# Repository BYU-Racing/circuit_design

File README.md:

# circuit_design
All of the low voltage circuit schematics and PCB designs

Deprecated designs are in the 2024 folder, all new stuff is in 2025

cheeseburger

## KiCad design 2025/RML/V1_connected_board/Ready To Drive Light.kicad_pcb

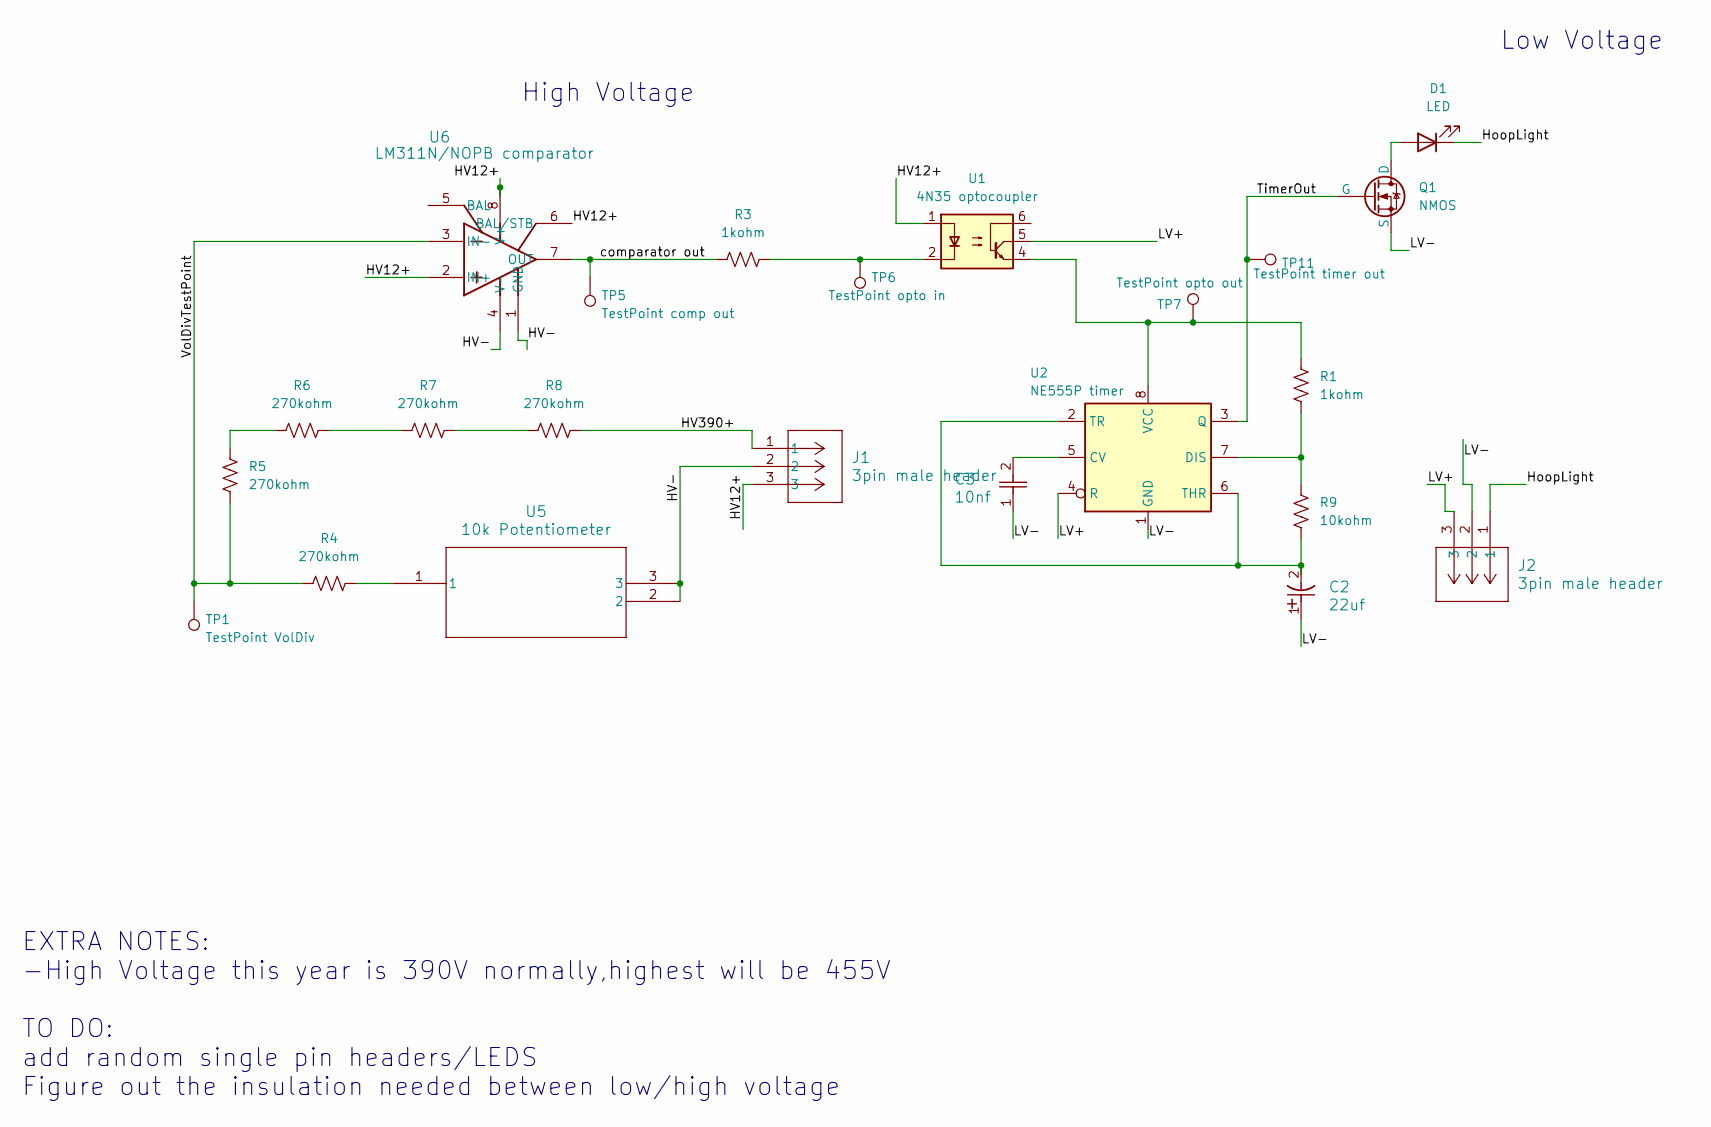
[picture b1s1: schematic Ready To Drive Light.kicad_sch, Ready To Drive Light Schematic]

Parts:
C2: 22uf; PCAP_16x20-THRU-ELECT_NCA
C3: 10nf; CAP_B32021_TDK
D1: LED; LED_D5.0mm_FlatTop
J1, J2: 3pin male header; CONN_G800W305xxxEU_AMP
Q1: NMOS; TO220AB_VIS
R1, R3: 1kohm; R_Axial_DIN0207_L6.3mm_D2.5mm_P7.62mm_Horizontal
R4, R5, R6, R7, R8: 270kohm; R_Axial_DIN0207_L6.3mm_D2.5mm_P7.62mm_Horizontal
R9: 10kohm; R_Axial_DIN0207_L6.3mm_D2.5mm_P7.62mm_Horizontal
TP1: TestPoint VolDiv; TestPoint_Loop_D2.60mm_Drill1.4mm_Beaded; PARTREV A
TP5: TestPoint comp out; TestPoint_Loop_D2.60mm_Drill1.4mm_Beaded
TP6: TestPoint opto in; TestPoint_Loop_D2.60mm_Drill1.4mm_Beaded
TP7: TestPoint opto out; TestPoint_Loop_D2.60mm_Drill1.4mm_Beaded
TP11: TestPoint timer out; TestPoint_Loop_D2.60mm_Drill1.4mm_Beaded
U1: 4N35 optocoupler; DIP-6_W7.62mm
U2: NE555P timer; DIP-8_W7.62mm
U5: 10k Potentiometer; 3296W-1-103_BRN
U6: LM311N/NOPB comparator; N08E

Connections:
/HV12+: J1.3, U1.1, U6.2 (IN+), U6.6 (BAL/STB), U6.8 (V+)
/HV390+: J1.1, R8.2
/HV-: J1.2, U5.2, U5.3, U6.1 (GND), U6.4 (V-)
/HoopLight: D1.1 (K), J2.1
/LV+: J2.3, U1.5, U2.4 (R)
/LV-: C2.1, C3.1, J2.2, Q1.3 (S), U2.1 (GND)
/TimerOut: Q1.2 (G), TP11.1, U2.3 (Q)
/VolDivTestPoint: R4.1, R5.1, TP1.1, U6.3 (IN-)
/comparator out: R3.1, TP5.1, U6.7 (OUT)
unnamed: D1.2 (A), Q1.1 (D)
unnamed: R3.2, TP6.1, U1.2
unnamed: R4.2, U5.1
unnamed: R5.2, R6.1
unnamed: R6.2, R7.1
unnamed: R7.2, R8.1
unnamed: C3.2, U2.5 (CV)
unnamed: R1.1, R9.2, U2.7 (DIS)
unnamed: C2.2, R9.1, U2.2 (TR), U2.6 (THR)
unnamed: R1.2, TP7.1, U1.4, U2.8 (VCC)

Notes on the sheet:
Low Voltage
EXTRA NOTES: -High Voltage this year is 390V normally,highest will be 455V TO DO: add random single pin headers/LEDS Figure out the insulation needed between low/high voltage
High Voltage

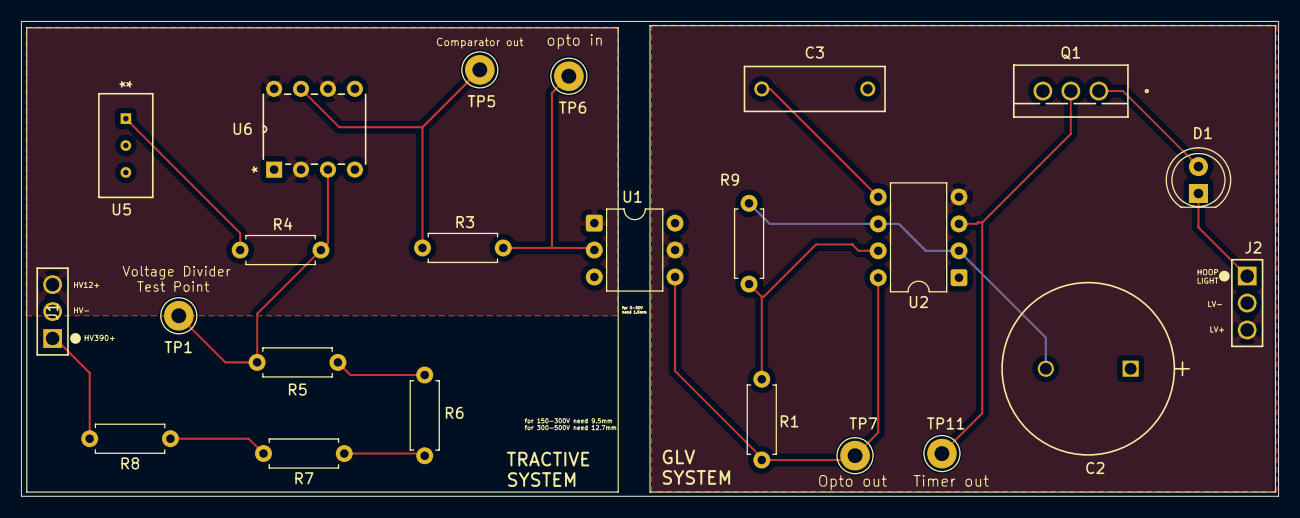
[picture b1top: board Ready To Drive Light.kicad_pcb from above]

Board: 2 copper layers, 118.6 x 44.8 mm, 23 parts (0 on the bottom side), 19 nets.

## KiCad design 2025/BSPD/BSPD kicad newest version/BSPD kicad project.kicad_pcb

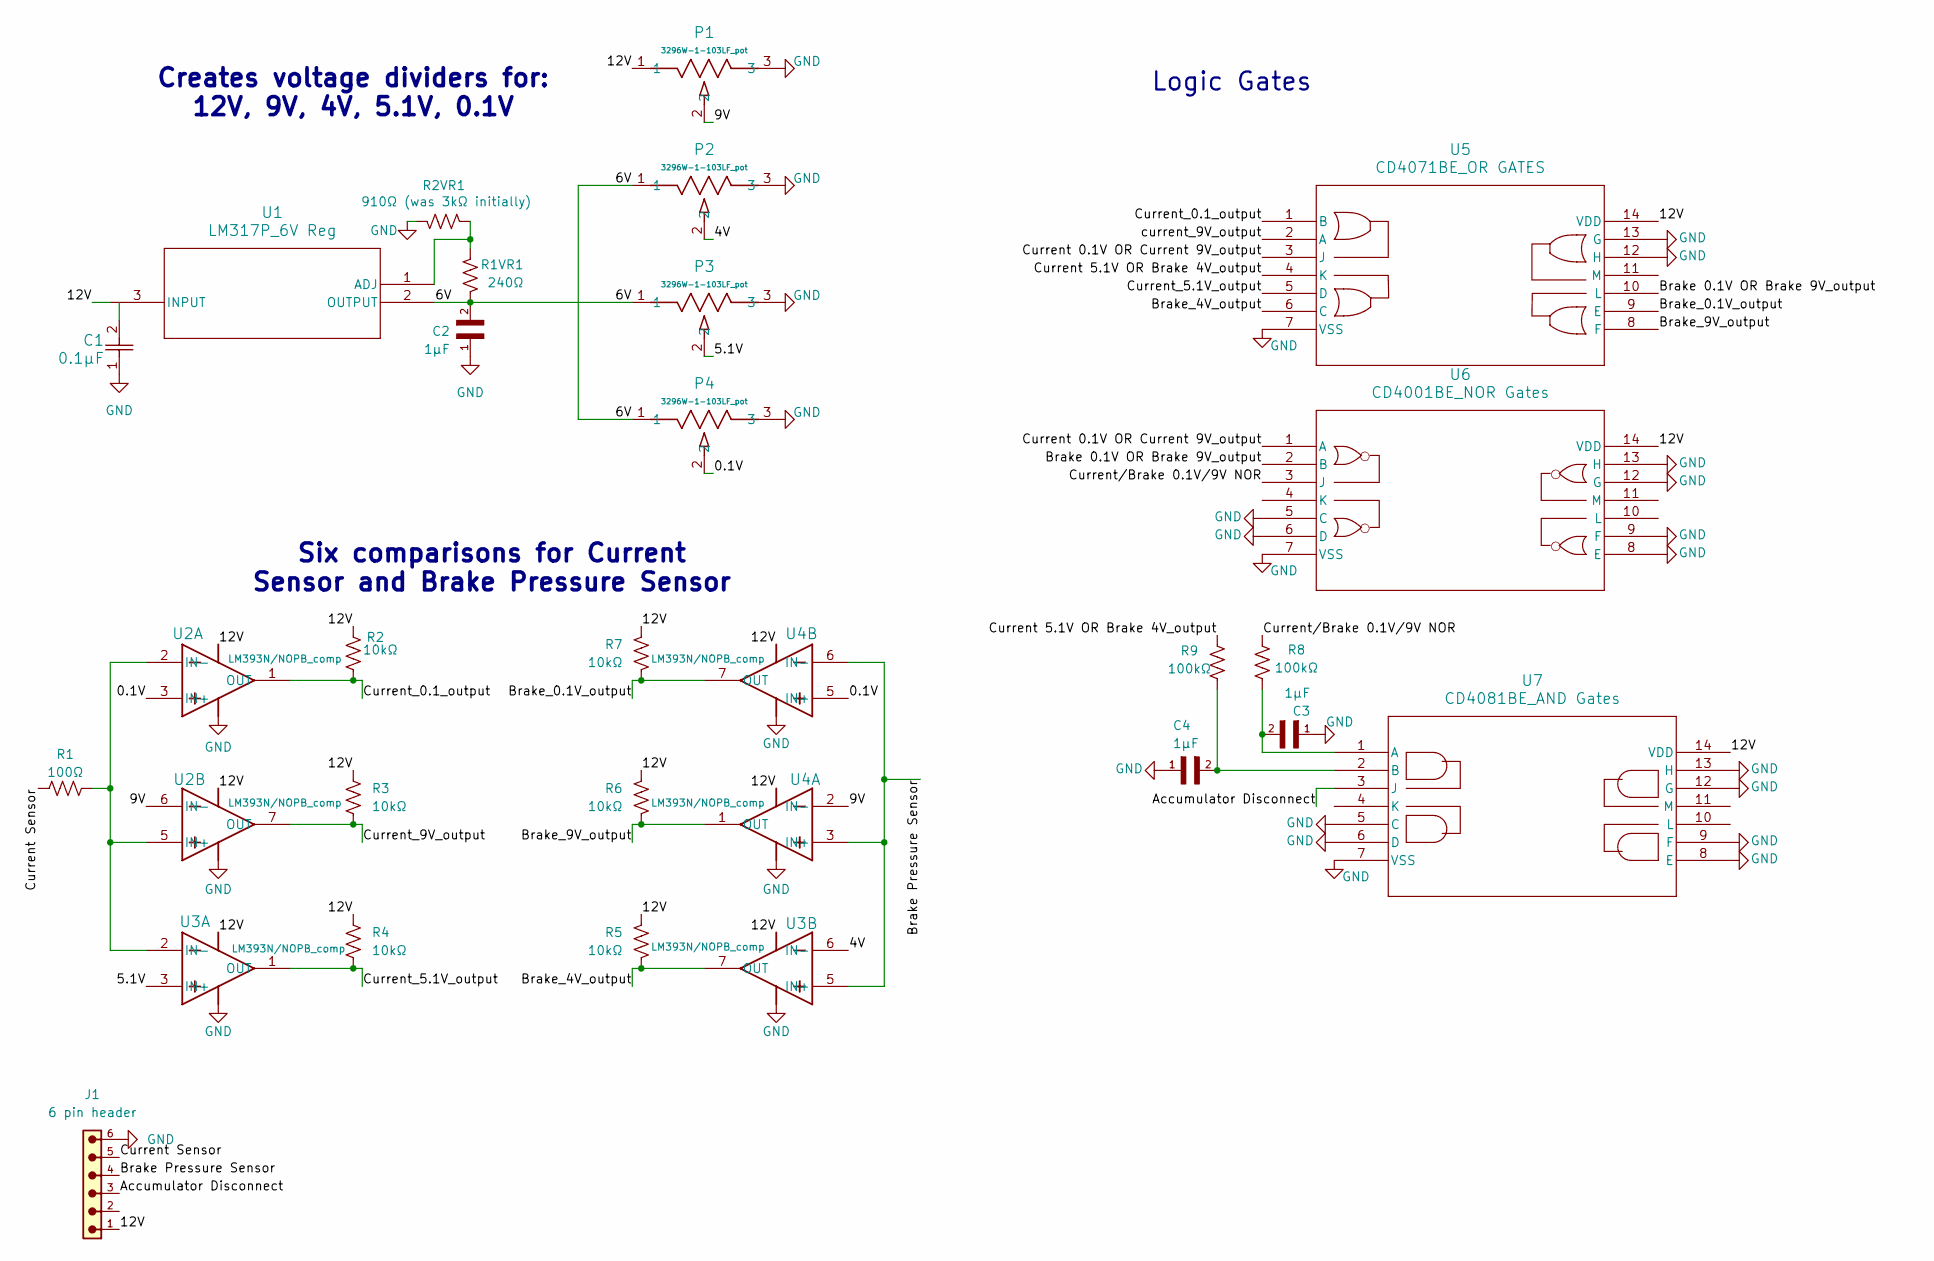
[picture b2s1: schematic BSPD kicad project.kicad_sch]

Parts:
C1: 0.1µF; K104K10X7RF5UH5_VIS
C2, C3, C4: 1µF; CAP_RCER72A105K2DBH03A; PARTREV Mar. 2018
J1: 6 pin header; PinHeader_1x06_P1.00mm_Vertical
P1, P2, P3, P4: 3296W-1-103LF_pot; POT_3296W
R1: 100Ω; R_Axial_DIN0204_L3.6mm_D1.6mm_P5.08mm_Horizontal
R1VR1: 240Ω; R_Axial_DIN0204_L3.6mm_D1.6mm_P5.08mm_Horizontal
R2, R3, R4, R5, R6, R7: 10kΩ; R_Axial_DIN0204_L3.6mm_D1.6mm_P5.08mm_Horizontal
R2VR1: 910Ω (was 3kΩ initially); R_Axial_DIN0204_L3.6mm_D1.6mm_P5.08mm_Horizontal
R8, R9: 100kΩ; R_Axial_DIN0204_L3.6mm_D1.6mm_P5.08mm_Horizontal
U1: LM317P_6V Reg; TO-220FP_STM
U2, U3, U4: LM393N/NOPB_comp; N08E
U5: CD4071BE_OR GATES; N14
U6: CD4001BE_NOR Gates; N14
U7: CD4081BE_AND Gates; N14

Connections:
/0.1V: P4.2, U2.3 (IN+), U4.5 (IN+)
/4V: P2.2, U3.6 (IN-)
/5.1V: P3.2, U3.3 (IN+)
/6V: C2.2, P2.1, P3.1, P4.1, R1VR1.2, U1.2 (OUTPUT)
/9V: P1.2, U2.6 (IN-), U4.2 (IN-)
/12V: J1.1, P1.1, R2.1, R3.1, R4.1, R5.1, R6.1, R7.1, U1.3 (INPUT), U5.14 (VDD), U6.14 (VDD), U7.14 (VDD)
/Accumulator Disconnect: J1.3, U7.3 (J)
/Brake 0.1V OR Brake 9V_output: U5.10 (L), U6.2 (B)
/Brake Pressure Sensor: J1.4, U3.5 (IN+), U4.3 (IN+), U4.6 (IN-)
/Brake_0.1V_output: R7.2, U4.7 (OUT), U5.9 (E)
/Brake_4V_output: R5.2, U3.7 (OUT), U5.6 (C)
/Brake_9V_output: R6.2, U4.1 (OUT), U5.8 (F)
/Current 0.1V OR Current 9V_output: U5.3 (J), U6.1 (A)
/Current 5.1V OR Brake 4V_output: R9.1, U5.4 (K)
/Current Sensor: J1.5, R1.1
/Current_0.1_output: R2.2, U2.1 (OUT), U5.1 (B)
/Current_5.1V_output: R4.2, U3.1 (OUT), U5.5 (D)
/Current_9V_output: R3.2, U2.7 (OUT)
/Current/Brake 0.1V/9V NOR: R8.1, U6.3 (J)
/current_9V_output: U5.2 (A)
GND: C1.1, C2.1, C3.1, C4.1, J1.6, P1.3, P2.3, P3.3, P4.3, R2VR1.1, U5.7 (VSS), U5.12 (H), U5.13 (G), U6.5 (C), U6.6 (D), U6.7 (VSS), U6.8 (E), U6.9 (F), U6.12 (G), U6.13 (H), U7.5 (C), U7.6 (D), U7.7 (VSS), U7.8 (E), U7.9 (F), U7.12 (G), U7.13 (H)
unnamed: R1VR1.1, R2VR1.2, U1.1 (ADJ)
unnamed: R1.2, U2.2 (IN-), U2.5 (IN+), U3.2 (IN-)
unnamed: C3.2, R8.2, U7.1 (A)
unnamed: C4.2, R9.2, U7.2 (B)

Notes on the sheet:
Six comparisons for Current Sensor and Brake Pressure Sensor
Logic Gates
Creates voltage dividers for: 12V, 9V, 4V, 5.1V, 0.1V

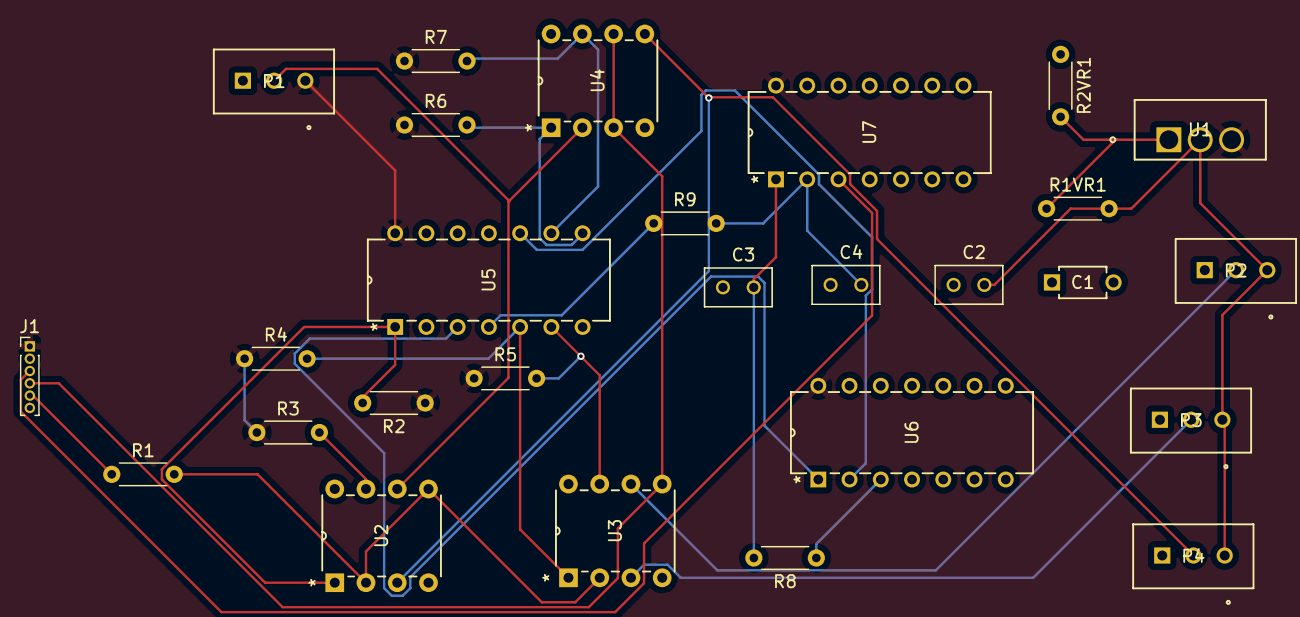
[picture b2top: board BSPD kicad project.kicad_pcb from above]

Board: 2 copper layers, 27 parts (0 on the bottom side), 24 nets.

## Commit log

2024-02-23 Dump car_software's PCB folder into new repository.
2024-02-23 Import strain gauge PCB.
2024-02-23 Add 4 pin header for teensy. Create and zip CAM files. Organize zipped files into gerber folder.
2024-02-27 Change all PCBs to have 12mm track widths. Remake gerber files. Cry.
2024-02-28 Import correct throttle control pcb. Remove incorrect throttle control pcb. Increase track width. Generate new gerber file for throttle control. Organize old eagle files. Rename PCB projects.
    mine house is a house of order
2024-02-28 Change all PCB track widths to 20mil. Generate new gerbers. Cry (again).
2024-02-29 Increase pad sizes and revise track routing in throttle control and ecu files. Make ecu gerber. Fiddle with ecu file and reduce board size, making streamlined gerber file. Make version txt file.
    i'm definitely not beating the caffeine dependency allegations
2024-03-01 Expand pads and generate new gerbers for strain gauge and dashboard pcbs.
2024-03-07 Move PCBs into new folder. Prepare to sacrifice soul to create new PCBs
    i am going to exPLODE
2024-03-27 Move PCB v3.0s into old folder. Create (blank) Master Schematic sheet. Prepare for the storm.
2024-04-05 Make footprints for accelerometer, GPS, 24-pin connector. Update master schem with things. Make test print gerber. The storm has arrived.
2024-04-05 Work a bit more on the master schematic. Revise footprints.
2024-04-08 Add more Teensys and parts. Still in progress.
2024-04-12 try to route teensy 1 pcb. get confused and sorta overwhelmed.
    ????????????????????????????????????????????????????????????????????????????????????????????????????????????????????????
2024-04-17 revise 24-pin footprint (drop to 16 pins, eliminate bottom layer pins and make top layer only). change connections and redo teensy 2 layout
2024-04-17 route teensy 1 pcb.
2024-04-19 finish TEENSY 1 routing. start on TEENSY 3-4 pcb.
2024-04-21 route teensy 2 and teensy 3-4 pcbs. complicated and requires careful checking of pinout. sorry fellas. add screw holes (M4 screws) to all PCBs.
2024-04-23 Revise PCB layouts/bring board dimensions to happy numbers. Move start switch circuit from TEENSY 3-4 to TEENSY 2. Add resistor to BLPS circuit for voltage divider.
2024-04-23 Revise layout for TEENSY 3-4. Generate gerbers for all PCBs.
2024-05-15 Resize 24-pin holes. Adjust can module orientation on teensy 3-4.
    need to make new gerber files but am waiting on input for 24-pin position on t3-4. may need to just figure out a better orientation for it
2024-09-22 create folders for 2024 season and 2025 season. create rough bspd schematic. go stupid. go crazy.
2024-09-25 Correct component selection, add potentiometers and voltage regulator. All for BSPD schematic
2024-09-25 Fiddle a bit with the BSPD schematic. Nothing crazy
2024-10-02 i don't remember what i did but i made changes.... they shouldn't affect anything though
2024-10-23 Add voltage regulators, replace comparators with correct part, add voltage rails for logic gates. Still need potentiometers...
2024-11-02 Add comparators. Reconfigure nets. Generate unrouted PCB board. Get jiggy with it
2024-11-07 tweak bspd. still not finished so ignore this for now....
2024-11-08 Add resistor and capacitor values for generic components. Ready for wiring!
2024-11-08 i forgor
2024-11-09 updates
    no clue what though
2024-11-15 Start routing things. Yippee!
2024-11-20 Finish routing BSPD. Need to add M3 mounting holes and a new plug
2024-11-28 reorganize board and reroute it. much smaller now :)
    wahoo
2024-12-04 Simplify/flesh out BSPD. Not finished.
    need to label output voltages on back of board, add PCBWay logo, and other things i don't remember rn... yeesh
2024-12-09 Finish BSPD. Add PCBWay and BYU logos for boards
2024-12-29 Create Schs for other PCBs. Add 5 gorbillion comments to the PCB BoM because I'm confused. Listen to church music. Eat some fudge from the fridge downstairs.
    christmas break is fun
2025-01-11 tweak BSPD per david's input. need to redo routing now. sad
2025-01-11 finish tweaking (the bspd, i'll never not be tweaking))
2025-01-15 Still getting schematics figured out. Need to swap out SMT stuff for THT
2025-01-15 Push... changes... that I made... apparently...
2025-01-17 Work a bit on DCF-ECU. Need to sort footprint sourcing for routing and pin holes. Aeugh.
    SO MUCH TO DO AAAAAAAAAAAAAAA
2025-01-17 Finally add the proper libraries. Altium itself may not have them shown/available to you'll have to fix that. Video coming soon I guess...
2025-01-17 Finish(?) routing the DCF-ECU. Stay up too late. Maybe make a breakthrough on 18 month-old classroom lessons.
2025-01-17 fix mosfet circuits. shoutout to joel and collin
2025-01-18 Make and sorta organize dcf board... sleepy....
2025-01-21 Route DCF-ECU. Finishing touches required...
2025-01-22 Add parts for hotbox and blackbox schematics. mess with dcf-ecu a bit (need to reroute and flip plugs)
2025-01-24 Add ground pins. YEP. that's it
2025-01-25 Add CAN VIAs. Redo polygons. Route plugs. Add mounting holes and graphics. Ready to rumble???
2025-01-25 Make BSPD pad sizes larger, reroute a bit as result of that.
2025-01-25 Add BYU Racing logo.
2025-01-25 Add BYU Racing logo and BSPD label. Organize some files a bit in the repo. Make BSPD gerber.
2025-01-29 Reroute and tweak some connections per Cole. Remove 5V plane, replace with 3.3V since there were more connections. Route 5V signals with bottom traces. Add... secrets....
    wahoo
2025-01-29 Initial Wiring Connections
2025-01-29 Initial PCB thinbg
2025-01-30 Adding the Steering Wheel Altium Files to Github
    No Gerber yet but Will generate those once I pass off the locations of the buttons with Ergo
2025-01-30 Fix CAN line routing. Expand pad sizes for teensys. Add some vias and change vias to pads for CAN extenders. Clean up some other messy routes. Watch streamers and get distracted
2025-01-30 Wire up DCR, mostly. The IMU needs an accurate footprint, inshallah snapeda will provide
2025-01-30 No changes were made, just made a dummy project for a how-to on alitum libraries.
2025-01-31 Prime schematic for wiring
2025-01-31 Add correct IMU footprint. needs a correctly space gps pin set
2025-01-31 Example time. Ignore.
2025-01-31 Reset all of it. A smart one is me
2025-01-31 Blake's Hotbox Schematic; having problems with getting CAN footprint.
2025-01-31 IMU footprint in folder.
2025-01-31 Blake's Hotbox schematic; CAN footprint won't load
2025-02-01 Schematic approved by Connor
2025-02-01 Maybe this works
2025-02-01 Import CAN Modules from whatever dark and secret place it hides in my Altium account
2025-02-01 I think this is good but also what do I know
2025-02-02 Cash money in the bank
2025-02-03 route pcb
2025-02-03 Add CAN Module footprint to PCB
2025-02-03 tweak pad sizes for V Regs. will have to make a new gerber file.
2025-02-03 forgot to save something so another push. wahoo
2025-02-03 Pad width update
2025-02-03 Circle on corner pins
2025-02-03 Should probably repour the ground plane lol
2025-02-03 Shaved off some mils
2025-02-03 Find correctly spaced GPS pin. Hopefully the pin spacing is correct or I will go ((( c r a z y )))
2025-02-04 Finished Protoype
2025-02-04 almost done routing, need 10 more minutes
2025-02-05 Route DCR. Put a stupid joke on the back of the board.
2025-02-05 don't say im afraid of commitment
2025-02-05 Add joke. Generate gerber. Less go?
2025-02-05 guess i saved... here we go
2025-02-05 Tweak pads and rules file for DRC. Generate gerber. Hooray
2025-02-05 Make gerber. Also record video
2025-02-05 Slim board down to make plugs fit better. Make new gerber
2025-02-05 Rules checks make me cry
2025-02-05 Jank AF solder pads but oh well
2025-02-05 Hahaha suck my nuts rule check
2025-02-05 Gerber go brrrr
2025-02-05 lols
2025-02-06 Final touches before first order
    added logos and gerber files
2025-02-06 Fix board. Add dumb thing. Yay
2025-02-06 Added WOX String and redid Gerber
2025-02-06 Last thing
2025-02-07 interim commit
2025-02-07 Generate footprints, including CAN module.
2025-02-07 Tweak pads and some routing things. Generate gerber. Shoutout bradford
2025-02-07 double checking R values. ignore
2025-02-07 Plugs go brr
2025-02-07 STOOOPP step file you're gonna get me in trouble
2025-02-07 Too many plugs, not enough drugs
2025-02-08 stepstepstepstep
2025-02-08 Exporting lul
2025-02-08 Watch your step
2025-02-08 One small step for man
2025-02-12 Hotbox Gerber files
2025-02-15 not sure what i did tbh but anyways
2025-02-21 add component...
2025-02-21 new gerber
2025-02-21 idk tbh...
2025-02-26 Make schematic for protoboard DCF
    aeugh
2025-02-28 Swap out SMD resistors for THT resistors. Remake gerbers. Rearrange graphics. Bing bing wahoo
2025-03-13 Add pull up resistors. Condense comparators. Start work on rerouting the dang thing. Aeugh
2025-03-19 reroute bspd.
2025-03-19 generate gerber
2025-03-26 Make changes to DCF-ECU. Realize it doesn't work. Cry. Prep branch for obsolesence
2025-03-26 Add component for that one thing
2025-03-26 Make DCFv2 project. Add plugs, teensy, regulator, other things. Need to confirm placement before routing
2025-03-26 Make ECU schematic. Replace 2-pin plugs for MOSFET circuits with 1 4-pin. Ready for review
2025-03-26 updated thing from me closing the dumb project
2025-03-26 rearrange some stuff
2025-03-27 Route board. Add debug vias and label pins on the bottom. Include space for can modules and the like. add m3 mounting holes. shrug a bit. need to add dumb jokes to it still...
2025-03-28 Route ECUv2. Add test points and labels. Good to go? Needs review
2025-03-28 Add resistor to 4PT2 for voltage divider. Update and route pcb.
2025-03-28 Adjust hole sizes and fix rule violations.
2025-03-28 idk... i just saved it
2025-03-28 Tweak pads a little bit, run DRC (passed)
2025-03-28 Remove GND and 3.3V signal planes, replace with trace and GND polygon. Review with Landon.
2025-03-28 Remove 3.3V and GND planes, replace with polygons. Add voltage dividers. Run and pass DRC. Check with Landon
2025-03-28 Generate gerber.
2025-03-28 Generate gerbers
2025-04-09 Revise schematic. 12V supply voltages only. Drop voltage regulators for 1 6V drop down, the pots can handle the rest methinks. Routing and verification remain.
2025-04-10 Continue work on BSPDv3. Delete old fab files
2025-04-10 intermediate. simple routing progress only
2025-04-11 Route BSPD. Make new gerber. Organize schematic
2025-04-18 fix schematic layout
2025-05-03 Fix comparator 2 inputs. BSPD should work now
2025-05-06 shift board position. that's it.
2025-06-05 get rid of nested folder
2025-06-05 verify BSPD, remove .DsnWrk file, remove extraneous plug library
2025-06-05 Generate new gerber for BSPDv4. It should work without the janky lil wires on the actual board
2025-06-05 forgot to save. kms
2025-06-05 get rid of nested DCFv2 folder. Verify everything else is updated and correct.
2025-07-02 Add BPSD_SMD board. It's the BSPD but with SMD components. Wired and routed. I did this for 7 hours today so I'm not making a gerber, that can be someone else's... privilege...
2025-07-02 Update board name
2025-07-04 Switch inputs then switch them back because I am silly
2026-01-15 added folder for kicad bspd
2026-01-15 added bspd kicad files and reorganized schematic
2026-01-21 added first version of Ready To Move Light (RML)
2026-01-21 made version one subdirectory
2026-01-21 cleaned up RML
2026-01-21 added V2 folders
2026-01-23 Added some parts and start the low side schematics.
2026-02-04 fully designed PCB of RML HV side, includes gerber files
2026-02-04 quick deletes of unnecessary files
2026-02-04 moving stuff around in Ready to Move Light
